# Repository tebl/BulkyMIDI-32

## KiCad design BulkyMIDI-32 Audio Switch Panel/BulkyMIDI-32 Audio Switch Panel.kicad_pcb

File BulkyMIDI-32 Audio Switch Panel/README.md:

# BulkyMIDI-32 Audio Switch Panel
This is a front-facing panel for controlling the *BulkyMIDI-32 Audio Switch*, while optional by design I find that it makes the system a lot more enjoyable in use and on my desk. The main PCB didn't have suffiecient room for the LEDs either, so if you'd like a little feedback on the currently active input channel. 

- [1> Building the device](#1-building-the-device)
  - [1.1> Soldering it together](#11-soldering-it-together)
- [2> Schematic](#2-schematic)
- [3> BOM](#3-bom)

# 1> Building the device
Building a device such as this assumes you have at least minor experience soldering things together, recommended is that you at the very least have access to a soldering station with adjustable temperature. If currently available, you should probably start with 60/40 rosin core solder as the lead-free alternatives tends to be a bit harder to work with.

With requirements for basic equipment sorted, we need to talk a bit about what you want to achieve while building this project. The reason I ask is that while you can build a functional *mt32-pi* using the module alone, you can also build the complete version of it - including front panels, faceplates that goes on the top as well as *extras*-module for additional functionality. 

Now that you know what you want to build, we can get started on the most expensive step in any build process - shopping! So, head on over to the [BOM](#3-bom)-section for some information on what kind of components that you'll need. While I would have liked to give you specific part numbers for "reputable" electronic part suppliers, I can't afford to shop there so I usually make due with what I can find on sites such as ebay, AliExpress and any similar sites that sell cheap chinese components. The downside to this is that I can't link to a part directly and expect it to stay listed, so you'll need to consider the description listed as suggested search terms.

## 1.1> Soldering it together

The construction of this unit should be fairly straight-forward, just take your time in order to make sure everything goes into place - more or less straight. I usually recommend starting by having a good look at the PCBs, try to figure out where all of the listed components go and in which orientation they go in (all of this should be clearly marked on the silkscreen). 

The first component to be added is the right-angle pin headers, these are soldered on the front side of the board instead of the component side. I've found that these are often somewhat warped, so I usually try to just solder the outer edges first, then reheat and adjust so that the plastic part sits completely flush against the board before tackling the remaining pins.

The next component to go on are the 8mm hex standoffs, they in particular need to be positioned so that a flat edge lines up with the lef and right edges of the PCB. As these are just nylon, I've made things slightly easier for myself by using a sharp knife to trim a bit off the vertical edges of them - in particular the one that sits just above the power LED.

Here I've simply inserted the LEDs into the footprints (longer pin goes into the round pad), the same goes for the six switches before adding the front panel to the front of it.  Continuing on with the LEDs I'll tack one of the pins into place, then while reheating the pin I'll try and push slightly on it to ensure that it is perfectly aligned with the holes on the front panel before soldering the remaining pin. The switches mostly stick to their expected alignment, but feel free to use the same method except that you push from the from.

The front panel have been removed again, mostly because it'll slightly be in the way when installing it onto the main [Audio Switch](https://github.com/tebl/BulkyMIDI-32/tree/main/BulkyMIDI-32%20Audio%20Switch) PCB. If you're a perfectionist like me, you may want to deal with some of the light bleed that you'll inevitably get between the LEDs.

The easiest solution for this came to me in the middle of a dark and stormy night, standard heat shrink tubing with a diameter of at least 5mm. Using an 8mm hex standoff as a guide and a sharp knife, I cut it up into 8mm segments that was then just put on top of the LEDs. If you have a hot air station you can shrink it a bit to keep it from falling off when the front panel is removed, but as long as it stays in place they should as well. 

# 2> Schematic
The supplied KiCad files should be sufficient as both a schematic and as a  starting point for ordering PCBs (basically you could just zip the contents of the export folder and upload that on a fabrication site), the schematic is also available in [PDF-format](https://github.com/tebl/BulkyMIDI-32/tree/main/documentation/schematic) and this is what you'll need to print and work your way through this things don't work as expected after assembly.

# 3> BOM
Most parts should be easy to get a hold of from your favourite local electronic component shop, but given that I don't have access to such shops where I live so everything was based on whatever I could get cheapest from eBay/AliExpress (free shipping, but plan on waiting 3-4 weeks for delivery). Components in parenthesis can be considered optional for features beyond the more basic functionality, but where's the fun in that? You deserve the complete package.

| Reference             | Item                                                              | Count | Order  |
| --------------------- | ----------------------------------------------------------------- | ----- | ------ |
| Panel PCB             | Fabricate using Gerber files                                      |     1 | PCBWay
| D1-D6                 | 5mm LEDs, preferably frosted (not the bright clear ones)          |     6 |
| J1                    | Standard right-angle pin header (2.54mm spacing)                  |     1 |
| SW1-SW6               | 6x6x12mm momentary button                                         |     6 |
| Mounting ****         | Nylon M3 hex standoffs 8mm (M-F)                                  |     4 |
| Mounting ****         | Nylon M3x6mm nylon screws                                         |     4 |
| Mounting ****         | Nylon M3x6mm nylon nuts                                           |     4 |

****) These are available in the form of kits usually advertised *M3 nylon standoff kit* which should contain most of what you'd need. I do however recommend that you pick up extra M-F standoffs of lengths 8mm and 20mm, as quite a lot of them will be used when building more than one module.

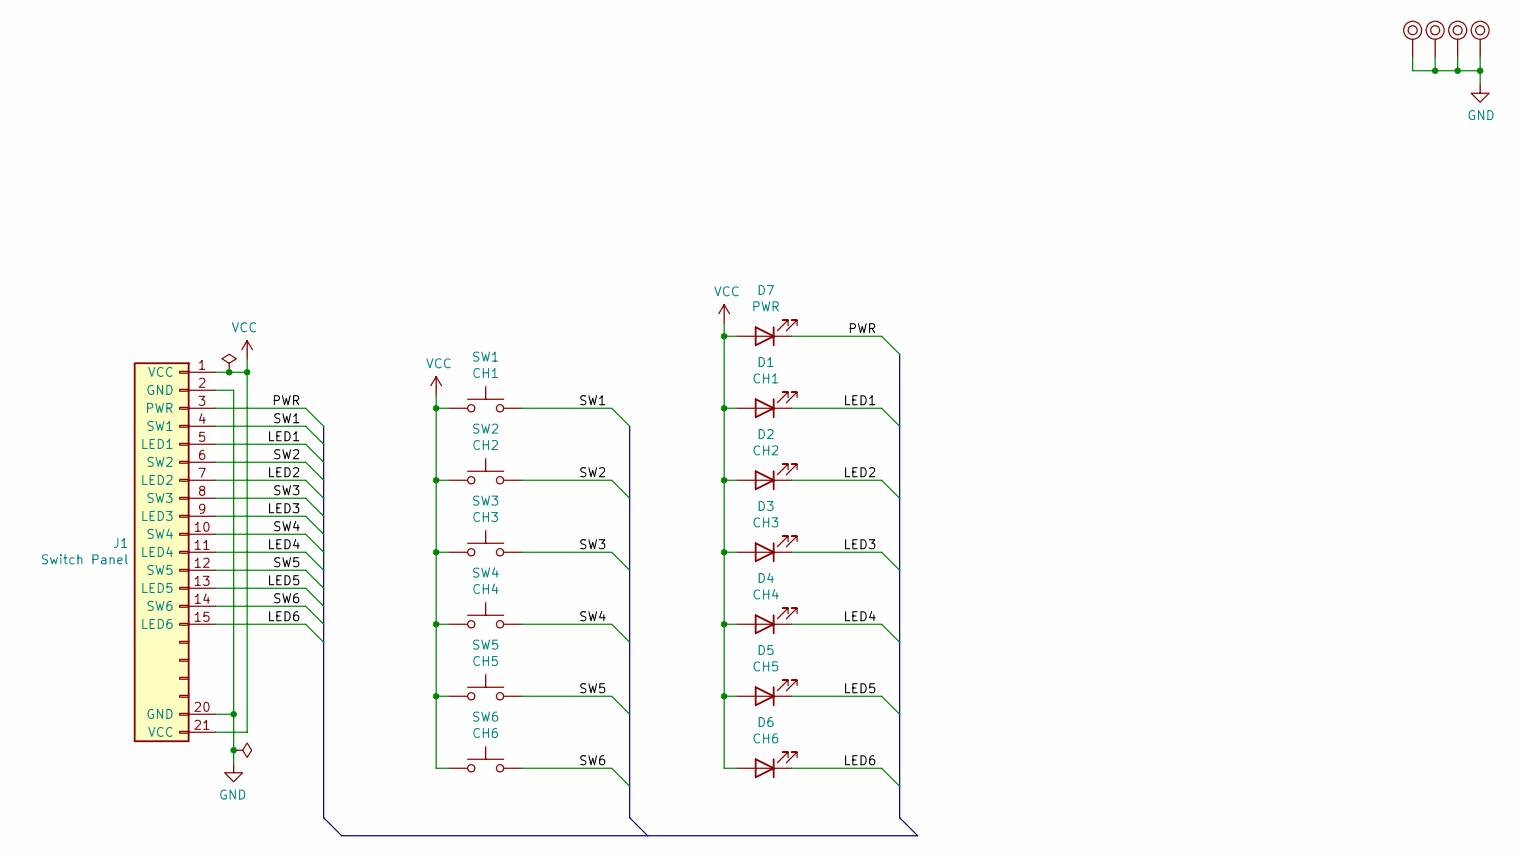
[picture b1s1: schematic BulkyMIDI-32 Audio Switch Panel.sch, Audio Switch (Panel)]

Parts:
D1: CH1; LED_D5.0mm
D2: CH2; LED_D5.0mm
D3: CH3; LED_D5.0mm
D4: CH4; LED_D5.0mm
D5: CH5; LED_D5.0mm
D6: CH6; LED_D5.0mm
D7: PWR; LED_D5.0mm
J1: Switch Panel; PinHeader_1x21_P2.54mm_Horizontal
M1, M2, M3, M4: Mounting_Pin; M3_pin
SW1: CH1; SW_PUSH_6mm
SW2: CH2; SW_PUSH_6mm
SW3: CH3; SW_PUSH_6mm
SW4: CH4; SW_PUSH_6mm
SW5: CH5; SW_PUSH_6mm
SW6: CH6; SW_PUSH_6mm

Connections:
/LED1: D1.1 (K), J1.5 (LED1)
/LED2: D2.1 (K), J1.7 (LED2)
/LED3: D3.1 (K), J1.9 (LED3)
/LED4: D4.1 (K), J1.11 (LED4)
/LED5: D5.1 (K), J1.13 (LED5)
/LED6: D6.1 (K), J1.15 (LED6)
/PWR: D7.1 (K), J1.3 (PWR)
/SW1: J1.4 (SW1), SW1.2
/SW2: J1.6 (SW2), SW2.2
/SW3: J1.8 (SW3), SW3.2
/SW4: J1.10 (SW4), SW4.2
/SW5: J1.12 (SW5), SW5.2
/SW6: J1.14 (SW6), SW6.2
GND: J1.2 (GND), J1.20 (GND), M1.1, M2.1, M3.1, M4.1
VCC: D1.2 (A), D2.2 (A), D3.2 (A), D4.2 (A), D5.2 (A), D6.2 (A), D7.2 (A), J1.1 (VCC), J1.21 (VCC), SW1.1, SW2.1, SW3.1, SW4.1, SW5.1, SW6.1

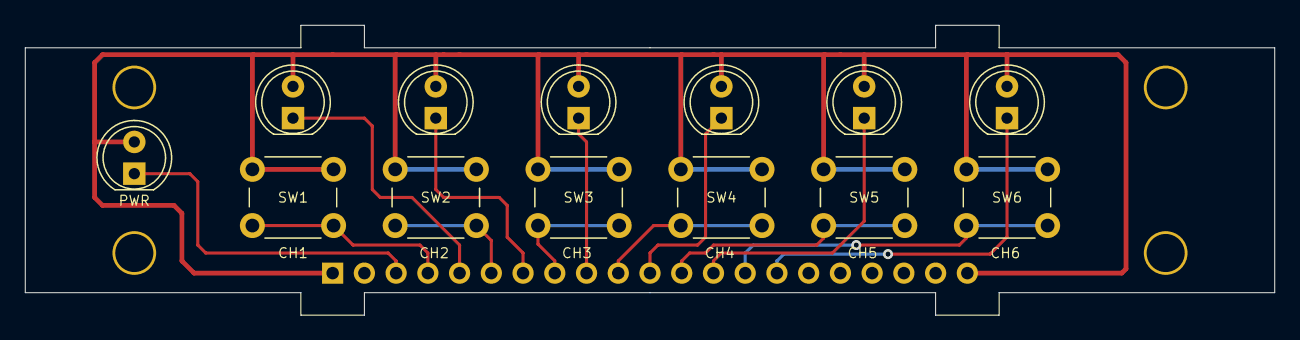
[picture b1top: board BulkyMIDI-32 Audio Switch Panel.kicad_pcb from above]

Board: 2 copper layers, 100.0 x 23.2 mm, 18 parts (1 on the bottom side), 15 nets.

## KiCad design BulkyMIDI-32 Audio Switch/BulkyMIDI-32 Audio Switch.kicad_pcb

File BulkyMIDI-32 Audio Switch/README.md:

# BulkyMIDI-32 Audio Switch
The complete *BulkyMIDI-32* consists of several separate PCB designs, many of them adding entirely separate functionality that can be used with or without the main unit. This specific module, once fully assembled will allow you to switch between six different audio inputs - think of it as the source selection switches on your stereo system.

I didn't want to use yet another MCU for what would account to an extremely trivial task such as this, neither did I want to switch the audio through a chip - so I instead went for simple flip-flops and somewhat exciting relays for each of the six channels.

- [1> Building the device](#1-building-the-device)
  - [1.1> Soldering it together](#11-soldering-it-together)
  - [1.2> Without front panel](#12-without-front-panel)
  - [1.3> Including front panel](#13-including-front-panel)
  - [1.4> Finishing touches](#14-finishing-touches)
- [2> Schematic](#2-schematic)
- [3> BOM](#3-bom)

# 1> Building the device
Building a device such as this assumes you have at least minor experience soldering things together, recommended is that you at the very least have access to a soldering station with adjustable temperature. If currently available, you should probably start with 60/40 rosin core solder as the lead-free alternatives tends to be a bit harder to work with.

With requirements for basic equipment sorted, we need to talk a bit about what you want to achieve while building this project. The reason I ask is that while you can build a functional *BulkyMIDI-32 Audio Switch* by using this module by itself, but there is certainly the option of building the complete version of it - including front panels, faceplates for the top of the unit and so on. 

Now that you know what you want to build, we can get started on the most expensive step in any build process - shopping! So, head on over to the [BOM](#3-bom)-section for some information on what kind of components that you'll need. While I would have liked to give you specific part numbers for "reputable" electronic part suppliers, I can't afford to shop there so I usually make due with what I can find on sites such as ebay, AliExpress and any similar sites that sell cheap chinese components. The downside to this is that I can't link to a part directly and expect it to stay listed, so you'll need to consider the description listed as suggested search terms.

## 1.1> Soldering it together
The construction of this unit should be fairly straight-forward, just take your time in order to make sure everything goes into place - more or less straight. I usually recommend starting by having a good look at the PCBs, try to figure out where all of the listed components go and in which orientation they go in (most of the information should be clearly marked on the silkscreen).

I will usually try to install components sorted by their physical size, doing it this way means you'll have an easier time keeping everything from looking somewhat crooked. This is your board, your build and you want it perfect - don't you? If you said no, then go sit in the corner because I worked hard on creating this for myself and whoever wants to build one.

Here we've already gotten started by installing all of the resistors needed, making sure that we use the correct values for each position on the board. While doing this, it is always a good recommendation to try and keep the colour bands in the same orientation - mostly because it makes it easier to spot mistakes later on. As I'm going to use this with a front panel, I've also taken the time to install the six 470 ohm resistors on the bottom of the board 

There are quite a few 1n4148 diodes in several locations on the board, these are polarized and for that reason we need to pay particular attention that the black band of the component matches up with those of the markings on the PCB.

Sockets should be installed for the singe IC needed for the complete unit. With that in place I've also installed the monolithic disc capacitors, these are all unpolarized and for the ones without any specific markings we will install 100nF capacitors (the code *104* will be printed on them). The single capacitor on the left edge of the board has a different value from the others, it is 22nF and will have the code *223* printed on it.

The next component we're going to install are the *2n3904* NPN-transistors, these have a flat side and a round side that needs to be matched to what is printed on the silkscreen - putting them in the wrong way around will usually create small smoke-bombs instead of their intended purpose. While there are components available that have pre-bent legs matching those on the footprint, I've not come across them at a reasonable price - so I just bend the legs outward myself and firmly push down on them until they sit a bit above the board.

Next up are the polarized capacitors, these need to go in the right way for them to function as expected. The stripe on the side of the capacitor denotes the negative side of it, this should be matched up with the filled in area of the footprint. When in doubt, just put the longer pin into the other hole (marked with a "+"). For the most part we won't be anywhere near any relevant voltage rating, but the higher rated ones will generally be physically larger - the one at *C2* should be rated at 16v or 25v, mainly as we physically won't have room for anything else.

Here we've added a common DC barrel connector (5.5mm x 2.1mm) to the board, followed by the six HK-19F-DC 5V relays. The relays have a tendency to come with crooked pins and we may need to do a bit of careful bending in order to get them into the board, there is also a little indent on one end that need to matched up with that on the board (similar to those of ICs).

I designed the board for a PJ-307 3.5mm stereo audio sockets, but as I didn't have enough of those in stock I used PJ-317 instead - they're a tight fit, but with the little nubs on the bottom cut off they sit well on the board. I've separated the six channel inputs from the single output by using differently coloured parts.

Depending on your life decisions up to this point, the assembly from this point continues in one or the other direction:
- [1.2> Without front panel](#12-without-front-panel)
- [1.3> Including front panel](#13-including-front-panel)

## 1.2> Without front panel

So you resisted the temptation to build the complete version, choosing instead to cut corners where possible? Well, that's OK too. I'm not judging, it was just a general observation.

There's not much that we need to do, mainly just install the single 3mm power LED (the longer LED goes into the round pad). The six switches are standard right-angle switches, the recommended way to install them is simply to solder a single pin then reheat and adjust its alignment before soldering in the rest of the pins.

If you have a faceplate, the board that goes on top of the unit, add some 20mm hex standoffs to each of the four corners before continuing on to the next part of the build.

- [1.4> Finishing touches](#14-finishing-touches)

## 1.3> Including front panel

The [Audio Switch Panel](https://github.com/tebl/BulkyMIDI-32/tree/main/BulkyMIDI-32%20Audio%20Switch%20Panel) have its own set of documentation going into the various steps required to put it together correctly, a finished unit looking like what is shown above. In particular we need to ensure that the hex standoffs have been aligned so that a *flat* side is lined up with the left and right edges of the board, the nuts on the back needs to have a similar flat side matched to the top and bottom. You may need to trim these slightly with a sharp knife or a file. 

Starting with installing 20mm standoffs, making sure that these have a *flat* side pointing towards the inside of the PCB. With the alignment correct you should be able to insert the panel into the board without too much force, then your selected faceplate is installed on top of the boards using screws. At this point we've not actually soldered them together yet, mostly to ensure that everything comes together correctly before we actually do so. Push the panel firmly so that it sits towards the back of the cutouts, then solder the pins into place - afterwards we just trim the excess parts of the pin headers.

When soldered, everything should stay where it should be and before continuing on we just remove the faceplate again before moving on to the next step.

- [1.4> Finishing touches](#14-finishing-touches)

## 1.4> Finishing touches

If you've made it this far, you're almost ready to simply start using it. What's missing in order to test it is the single IC that needs to be inserted into the socket, so just get that out of the way before you forget to do so. The device is powered using a 5v DC barrel jack (center positive). These should be easy to obtain from your favourite electronics vendor, just make sure that it's from a somewhat respected brand.

The only step that's remaining is to just screw the faceplates back on the top of the device, once that's in place we can also add the front panel as well. With those in place we're ready to start planning the next project, quite possibly while playing some music through the audio switch.

# 2> Schematic
The supplied KiCad files should be sufficient as both a schematic and as a  starting point for ordering PCBs (basically you could just zip the contents of the export folder and upload that on a fabrication site), the schematic is also available in [PDF-format](https://github.com/tebl/BulkyMIDI-32/tree/main/documentation/schematic) and this is what you'll need to print and work your way through this things don't work as expected after assembly.

# 3> BOM
Most parts should be easy to get a hold of from your favourite local electronic component shop, but given that I don't have access to such shops where I live so everything was based on whatever I could get cheapest from eBay/AliExpress (free shipping, but plan on waiting 3-4 weeks for delivery). Components in parenthesis can be considered optional for features beyond the more basic functionality, but where's the fun in that? You deserve the complete package.

| Reference             | Item                                                              | Count | Order  |
| --------------------- | ----------------------------------------------------------------- | ----- | ------ |
| PCB                   | Fabricate using Gerber files                                      |     1 | [PCBWay](https://www.pcbway.com/project/shareproject/BulkyMIDI_32_Audio_Switch_118316c8.html)
| [Panel PCB](https://github.com/tebl/BulkyMIDI-32/tree/main/BulkyMIDI-32%20Audio%20Switch%20Panel) | Fabricate using Gerber files                                      |    (1)| [PCBWay](https://www.pcbway.com/project/shareproject/BulkyMIDI_32_Audio_Switch_Panel_a10b5ecb.html)
| C1,C3-C6,C7-C9        | 100nF ceramic capacitor (5mm)                                     |     7 |
| C2,C11                | 10uF electrolytic capacitor (4mm x 2mm)                           |     2 |
| C6                    | 470uF electrolytic capacitor (8mm x 3.5mm)                        |     1 |
| C10                   | 22nF ceramic capacitor (5mm)                                      |     1 |
| D1-D6,D10-D12,D16-D18 | 1N4148N small signal diode (DO-35)                                |    12 |
| D19 *                 | 3mm LED                                                           |    (1)|
| J1                    | 2.1mm x 5.5mm barrel plug                                         |     1 |
| J2,J3,J5,J7-J9        | PJ-307 3.5mm socket (alternatively PJ-317)                        |     7 |
| K1-K6                 | HK19F-DC5V relay                                                  |     6 |
| Q1-Q6                 | 2N3904 transistor (TO-92)                                         |     6 |
| R16-R18,R25-R27 *     | 470 ohm resistor                                                  |    (6)|
| R10-R12,R19-R21       | 1k ohm resistor                                                   |     6 |
| R7,R9,R13-R15,R22-R24 | 10k ohm resistor                                                  |     8 |
| R1-R6,R8              | 100k ohm resistor                                                 |     7 |
| SW1-SW6 *             | 6x6x5mm right-angle momentary button                              |    (6)|
| U1                    | CD40174BE (DIP-16)                                                |     1 |
| Mounting ****         | Nylon M3 hex standoffs 20mm (M-F)                                 |     4 |
| Mounting ****         | Nylon M3x6mm nylon screws                                         |     4 |
| Mounting ****         | Nylon M3x6mm nylon nuts                                           |     4 |

*) You can choose to install a front panel, in which case you would skip the installation of the 3mm LED as well as the switches. The resistors will be used by the front panel.

****) These are available in the form of kits usually advertised *M3 nylon standoff kit* which should contain most of what you'd need. I do however recommend that you pick up extra M-F standoffs of lengths 8mm and 20mm, as quite a lot of them will be used when building more than one module.

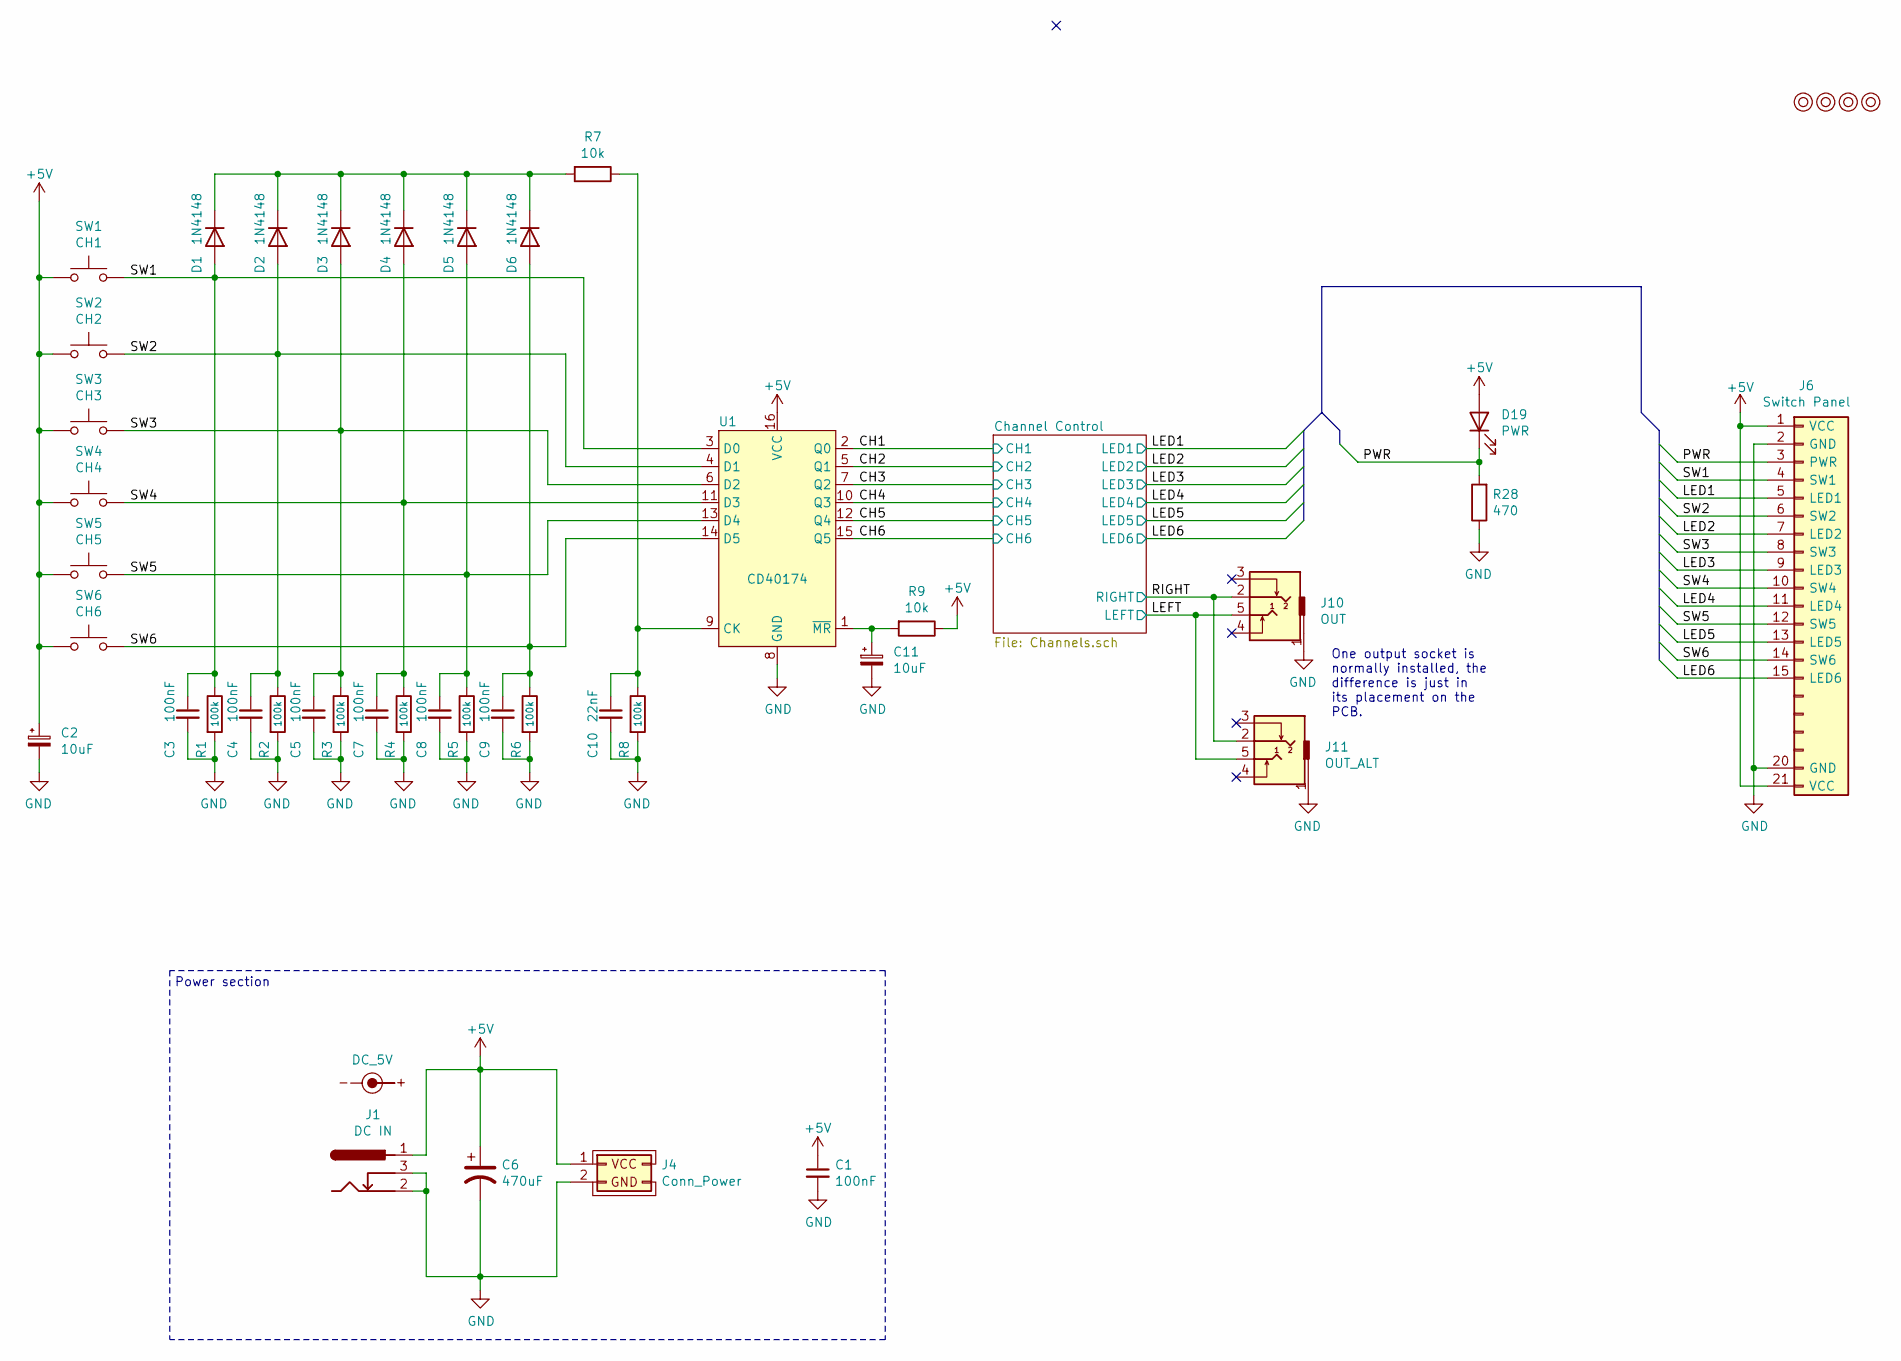
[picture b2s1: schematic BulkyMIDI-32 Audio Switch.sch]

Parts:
C1, C3, C4, C5, C7, C8, C9: 100nF; C_Disc_D4.7mm_W2.5mm_P5.00mm
C2, C11: 10uF; CP_Radial_D4.0mm_P2.00mm
C6: 470uF; CP_Radial_D8.0mm_P3.50mm
C10: 22nF; C_Disc_D4.7mm_W2.5mm_P5.00mm
D1, D2, D3, D4, D5, D6: 1N4148; D_DO-35_SOD27_P7.62mm_Horizontal
D19: PWR; LED_D3.0mm
J1: DC IN; BARREL_JACK
J4: Conn_Power
J6: Switch Panel; Switch_Panel
J10: OUT; Tayda_3.5mm_stereo_TRS_jack_A-853
J11: OUT_ALT; Tayda_3.5mm_stereo_TRS_jack_A-853
M1, M2, M3, M4: Mounting; M3
R1, R2, R3, R4, R5, R6, R8: 100k; R_Axial_DIN0207_L6.3mm_D2.5mm_P10.16mm_Horizontal
R7, R9: 10k; R_Axial_DIN0207_L6.3mm_D2.5mm_P10.16mm_Horizontal
R28: 470; R_Axial_DIN0207_L6.3mm_D2.5mm_P10.16mm_Horizontal
SW1: CH1; SW_Tactile_SPST_Angled_PTS645Vx39-2LFS
SW2: CH2; SW_Tactile_SPST_Angled_PTS645Vx39-2LFS
SW3: CH3; SW_Tactile_SPST_Angled_PTS645Vx39-2LFS
SW4: CH4; SW_Tactile_SPST_Angled_PTS645Vx39-2LFS
SW5: CH5; SW_Tactile_SPST_Angled_PTS645Vx39-2LFS
SW6: CH6; SW_Tactile_SPST_Angled_PTS645Vx39-2LFS
SYM1: DC_5V; PWR_Specification
U1: CD40174; DIP-16_W7.62mm_Socket_LongPads

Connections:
+5V: C1.1, C2.1, C6.1, D19.2 (A), J1.1, J4.1 (VCC), J6.1 (VCC), J6.21 (VCC), R9.1, SW1.2, SW2.2, SW3.2, SW4.2, SW5.2, SW6.2, U1.16 (VCC); also elsewhere on the board
/CH1: U1.2 (Q0); also elsewhere on the board
/CH2: U1.5 (Q1); also elsewhere on the board
/CH3: U1.7 (Q2); also elsewhere on the board
/CH4: U1.10 (Q3); also elsewhere on the board
/CH5: U1.12 (Q4); also elsewhere on the board
/CH6: U1.15 (Q5); also elsewhere on the board
/LED1: J6.5 (LED1); also elsewhere on the board
/LED2: J6.7 (LED2); also elsewhere on the board
/LED3: J6.9 (LED3); also elsewhere on the board
/LED4: J6.11 (LED4); also elsewhere on the board
/LED5: J6.13 (LED5); also elsewhere on the board
/LED6: J6.15 (LED6); also elsewhere on the board
/LEFT: J10.5, J11.5; also elsewhere on the board
/PWR: D19.1 (K), J6.3 (PWR), R28.2
/RIGHT: J10.2, J11.2; also elsewhere on the board
/SW1: C3.1, D1.2 (A), J6.4 (SW1), R1.1, SW1.1, U1.3 (D0)
/SW2: C4.1, D2.2 (A), J6.6 (SW2), R2.1, SW2.1, U1.4 (D1)
/SW3: C5.1, D3.2 (A), J6.8 (SW3), R3.1, SW3.1, U1.6 (D2)
/SW4: C7.1, D4.2 (A), J6.10 (SW4), R4.1, SW4.1, U1.11 (D3)
/SW5: C8.1, D5.2 (A), J6.12 (SW5), R5.1, SW5.1, U1.13 (D4)
/SW6: C9.1, D6.2 (A), J6.14 (SW6), R6.1, SW6.1, U1.14 (D5)
GND: C1.2, C2.2, C3.2, C4.2, C5.2, C6.2, C7.2, C8.2, C9.2, C10.2, C11.2, J1.2, J1.3, J4.2 (GND), J6.2 (GND), J6.20 (GND), J10.1, J11.1, R1.2, R2.2, R3.2, R4.2, R5.2, R6.2, R8.2, R28.1, U1.8 (GND); also elsewhere on the board
unnamed: C10.1, R7.1, R8.1, U1.9 (CK)
unnamed: C11.1, R9.2, U1.1 (~MR)
unnamed: D1.1 (K), D2.1 (K), D3.1 (K), D4.1 (K), D5.1 (K), D6.1 (K), R7.2

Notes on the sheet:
Power section
One output socket is normally installed, the difference is just in its placement on the PCB.

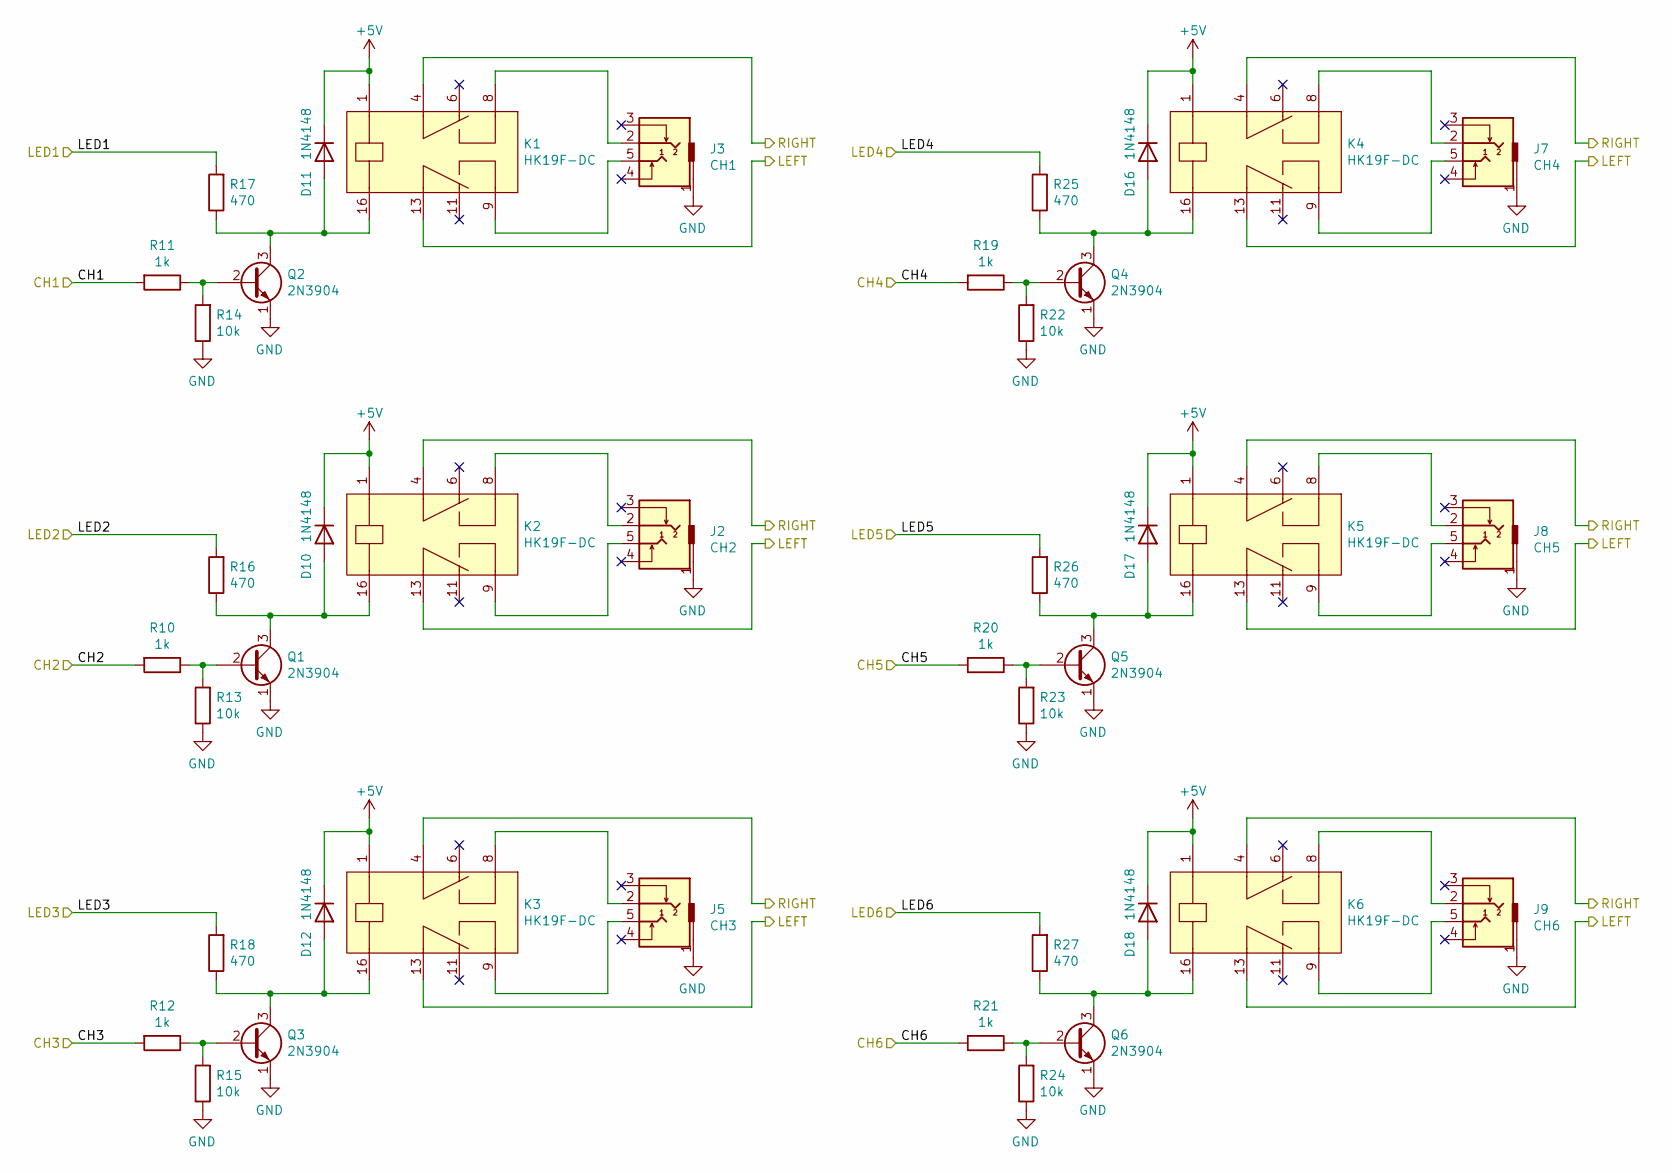
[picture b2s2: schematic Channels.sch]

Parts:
D10, D11, D12, D16, D17, D18: 1N4148; D_DO-35_SOD27_P7.62mm_Horizontal
J2: CH2; Tayda_3.5mm_stereo_TRS_jack_A-853
J3: CH1; Tayda_3.5mm_stereo_TRS_jack_A-853
J5: CH3; Tayda_3.5mm_stereo_TRS_jack_A-853
J7: CH4; Tayda_3.5mm_stereo_TRS_jack_A-853
J8: CH5; Tayda_3.5mm_stereo_TRS_jack_A-853
J9: CH6; Tayda_3.5mm_stereo_TRS_jack_A-853
K1, K2, K3, K4, K5, K6: HK19F-DC
Q1, Q2, Q3, Q4, Q5, Q6: 2N3904; TO-92_Inline_Wide
R10, R11, R12, R19, R20, R21: 1k; R_Axial_DIN0207_L6.3mm_D2.5mm_P10.16mm_Horizontal
R13, R14, R15, R22, R23, R24: 10k; R_Axial_DIN0207_L6.3mm_D2.5mm_P10.16mm_Horizontal
R16, R17, R18, R25, R26, R27: 470; R_Axial_DIN0207_L6.3mm_D2.5mm_P10.16mm_Horizontal

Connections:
+5V: D10.1 (K), D11.1 (K), D12.1 (K), D16.1 (K), D17.1 (K), D18.1 (K), K1.1, K2.1, K3.1, K4.1, K5.1, K6.1; also elsewhere on the board
/CH1: R11.2; also elsewhere on the board
/CH2: R10.2; also elsewhere on the board
/CH3: R12.2; also elsewhere on the board
/CH4: R19.2; also elsewhere on the board
/CH5: R20.2; also elsewhere on the board
/CH6: R21.2; also elsewhere on the board
/LED1: R17.2; also elsewhere on the board
/LED2: R16.2; also elsewhere on the board
/LED3: R18.2; also elsewhere on the board
/LED4: R25.2; also elsewhere on the board
/LED5: R26.2; also elsewhere on the board
/LED6: R27.2; also elsewhere on the board
/LEFT: K1.13 (COM_2), K2.13 (COM_2), K3.13 (COM_2), K4.13 (COM_2), K5.13 (COM_2), K6.13 (COM_2); also elsewhere on the board
/RIGHT: K1.4 (COM_1), K2.4 (COM_1), K3.4 (COM_1), K4.4 (COM_1), K5.4 (COM_1), K6.4 (COM_1); also elsewhere on the board
GND: J2.1, J3.1, J5.1, J7.1, J8.1, J9.1, Q1.1 (E), Q2.1 (E), Q3.1 (E), Q4.1 (E), Q5.1 (E), Q6.1 (E), R13.1, R14.1, R15.1, R22.1, R23.1, R24.1; also elsewhere on the board
unnamed: D10.2 (A), K2.16, Q1.3 (C), R16.1
unnamed: D11.2 (A), K1.16, Q2.3 (C), R17.1
unnamed: D12.2 (A), K3.16, Q3.3 (C), R18.1
unnamed: D16.2 (A), K4.16, Q4.3 (C), R25.1
unnamed: D17.2 (A), K5.16, Q5.3 (C), R26.1
unnamed: D18.2 (A), K6.16, Q6.3 (C), R27.1
unnamed: J2.2, K2.8 (NO_1)
unnamed: J2.5, K2.9 (NO_2)
unnamed: J3.2, K1.8 (NO_1)
unnamed: J3.5, K1.9 (NO_2)
unnamed: J5.2, K3.8 (NO_1)
unnamed: J5.5, K3.9 (NO_2)
unnamed: J7.2, K4.8 (NO_1)
unnamed: J7.5, K4.9 (NO_2)
unnamed: J8.2, K5.8 (NO_1)
unnamed: J8.5, K5.9 (NO_2)
unnamed: J9.2, K6.8 (NO_1)
unnamed: J9.5, K6.9 (NO_2)
unnamed: Q1.2 (B), R10.1, R13.2
unnamed: Q2.2 (B), R11.1, R14.2
unnamed: Q3.2 (B), R12.1, R15.2
unnamed: Q4.2 (B), R19.1, R22.2
unnamed: Q5.2 (B), R20.1, R23.2
unnamed: Q6.2 (B), R21.1, R24.2

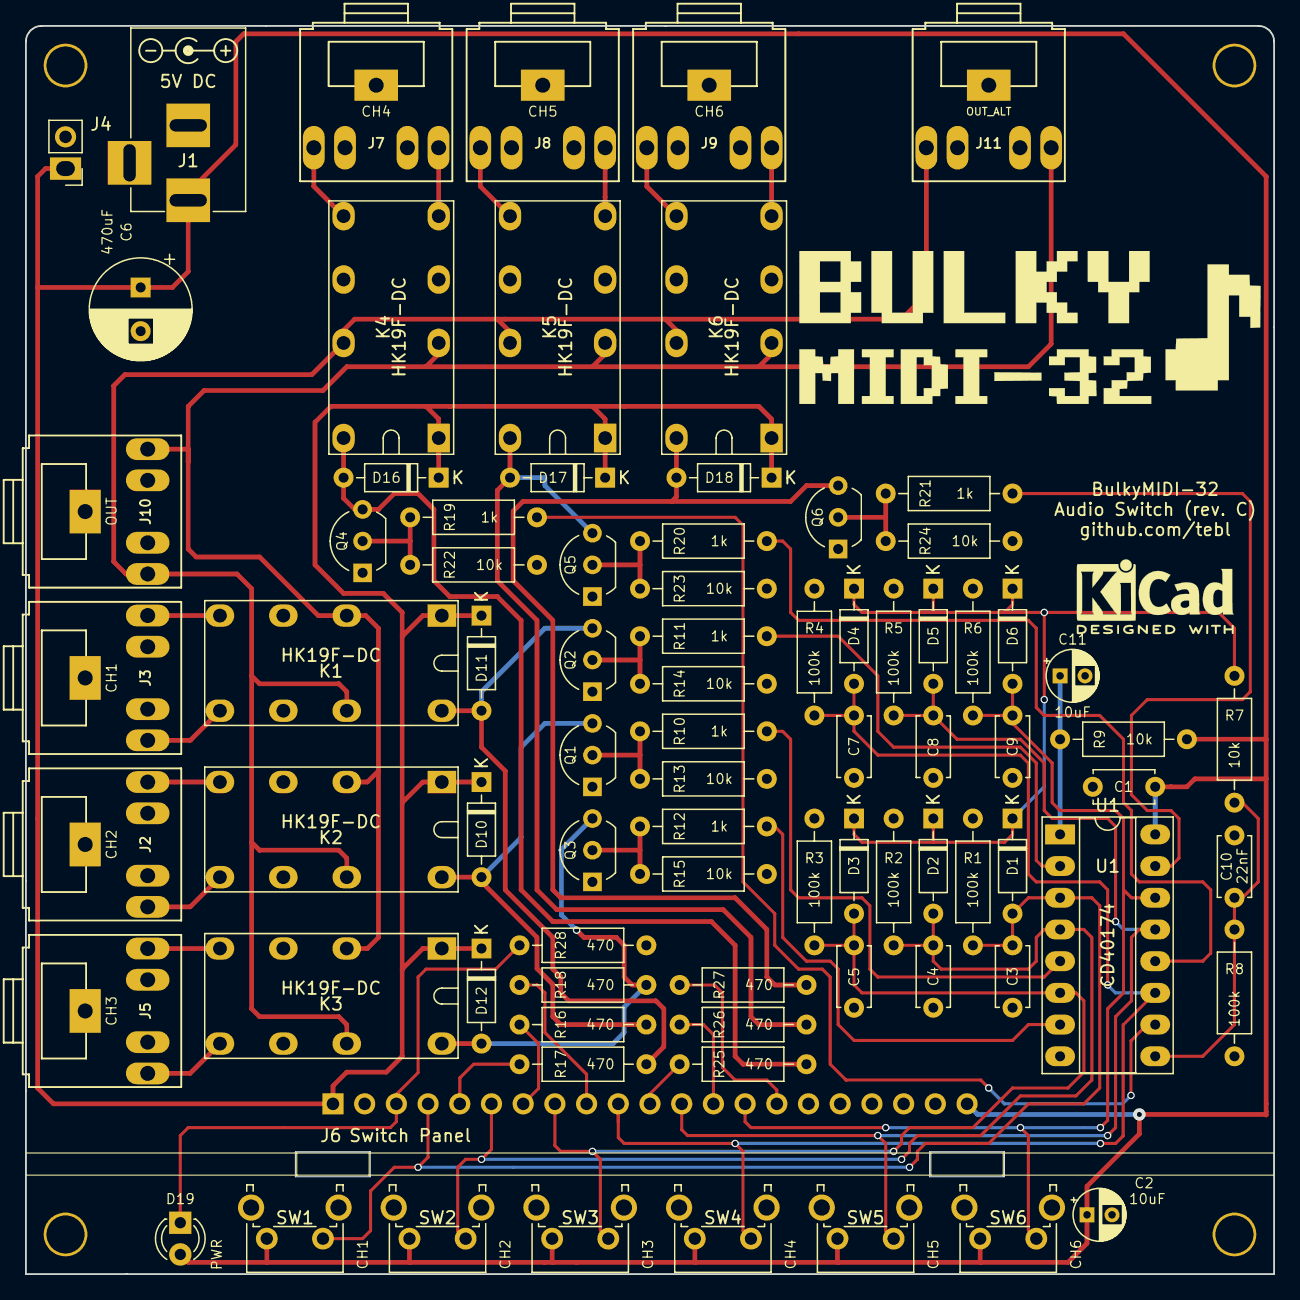
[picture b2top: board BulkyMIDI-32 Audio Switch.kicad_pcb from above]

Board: 2 copper layers, 100.0 x 100.0 mm, 87 parts (0 on the bottom side), 50 nets.
